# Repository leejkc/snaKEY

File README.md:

### todo list:

1. pcb borders
2. lcd/oled display
3. plate/case (3d print or order cnc)

### 50%, staggered, wired only

- **1** raspberry pi pico / pico2
- **47** diodes *(1N4148)*
- **47** switches
- **1** 2u plate mount stab (enter)
- **1** 6.25u plate mount stab
- keycaps

### LAYOUT:
[permalink to layout editor](https://www.keyboard-layout-editor.com/##@@=Esc&=Q&=W&=E&=R&=T&=Y&=U&=I&=O&=P&=%7B%0A%5B&=%7D%0A%5D&_x:0.25%3B&=Del%3B&@_w:1.25%3B&=Fn&=A&=S&=D&=F&=G&=H&=J&=K&=L&=%2F:%0A%2F%3B&=%22%0A'&_w:2%3B&=Enter%3B&@_w:1.75%3B&=Shift&=Z&=X&=C&=V&=B&=N&=M&=%3C%0A,&=%3E%0A.&=%3F%0A%2F%2F&=%E2%86%91&_w:1.5%3B&=%7C%0A%5C%3B&@_x:0.75&w:1.25%3B&=Ctrl&_w:1.25%3B&=Alt&_a:7&w:6.25%3B&=&_a:4&w:1.25%3B&=Super&=%E2%86%90&=%E2%86%93&=%E2%86%92)

note: **enter key has to be the 2u numberpad one**

### CAD DRAWINGS:

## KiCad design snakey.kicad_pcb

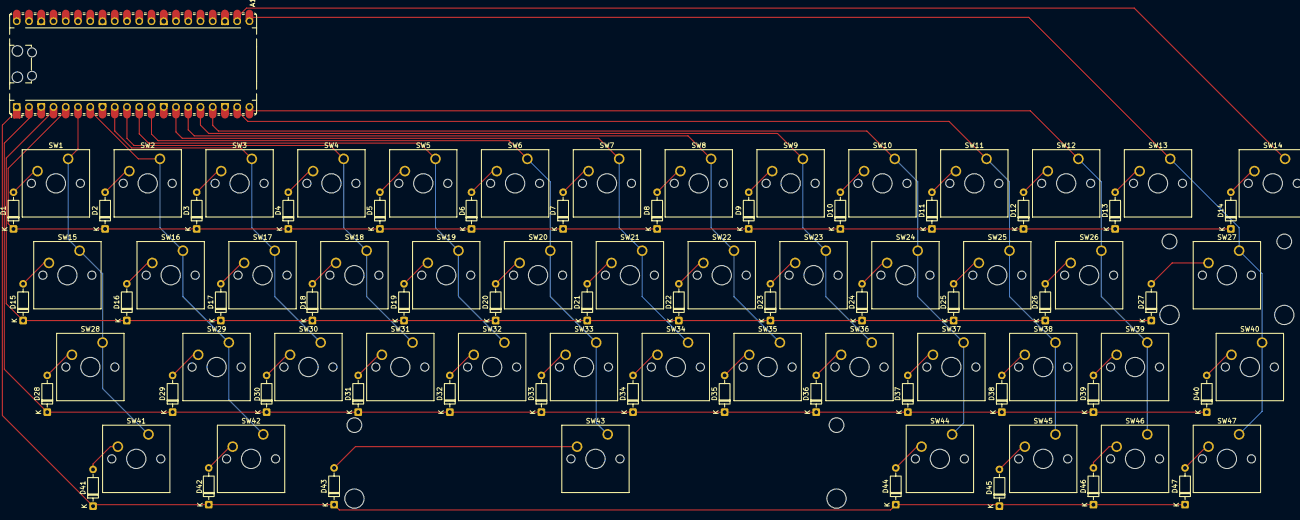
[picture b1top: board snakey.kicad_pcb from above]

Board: 2 copper layers, 95 parts (0 on the bottom side), 18 nets.

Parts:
A1: RaspberryPi_Pico; RaspberryPi_Pico_Common_Unspecified
D1, D2, D3, D4, D5, D6, D7, D8, D9, D10, D11, D12, D13, D14, D15, D16, D17, D18, D19, D20, D21, D22, D23, D24, D25, D26, D27, D28, D29, D30, D31, D32, D33, D34, D35, D36, D37, D38, D39, D40, D41, D42, D43, D44, D45, D46, D47: 1N4148; D_DO-35_SOD27_P7.62mm_Horizontal
SW1: ESC; SW_Cherry_MX_1.00u_PCB
SW2: q; SW_Cherry_MX_1.00u_PCB
SW3: w; SW_Cherry_MX_1.00u_PCB
SW4: e; SW_Cherry_MX_1.00u_PCB
SW5: r; SW_Cherry_MX_1.00u_PCB
SW6: t; SW_Cherry_MX_1.00u_PCB
SW7: y; SW_Cherry_MX_1.00u_PCB
SW8: u; SW_Cherry_MX_1.00u_PCB
SW9: i; SW_Cherry_MX_1.00u_PCB
SW10: o; SW_Cherry_MX_1.00u_PCB
SW11: p; SW_Cherry_MX_1.00u_PCB
SW12: [; SW_Cherry_MX_1.00u_PCB
SW13: ]; SW_Cherry_MX_1.00u_PCB
SW14: DEL; SW_Cherry_MX_1.00u_PCB
SW15: FN; SW_Cherry_MX_1.25u_PCB
SW16: a; SW_Cherry_MX_1.00u_PCB
SW17: s; SW_Cherry_MX_1.00u_PCB
SW18: d; SW_Cherry_MX_1.00u_PCB
SW19: f; SW_Cherry_MX_1.00u_PCB
SW20: g; SW_Cherry_MX_1.00u_PCB
SW21: h; SW_Cherry_MX_1.00u_PCB
SW22: j; SW_Cherry_MX_1.00u_PCB
SW23: k; SW_Cherry_MX_1.00u_PCB
SW24: l; SW_Cherry_MX_1.00u_PCB
SW25: ;; SW_Cherry_MX_1.00u_PCB
SW26: '; SW_Cherry_MX_1.00u_PCB
SW27: ENTER; SW_Cherry_MX_2.00u_PCB
SW28: SHIFT; SW_Cherry_MX_1.75u_PCB
SW29: z; SW_Cherry_MX_1.00u_PCB
SW30: x; SW_Cherry_MX_1.00u_PCB
SW31: c; SW_Cherry_MX_1.00u_PCB
SW32: v; SW_Cherry_MX_1.00u_PCB
SW33: b; SW_Cherry_MX_1.00u_PCB
SW34: n; SW_Cherry_MX_1.00u_PCB
SW35: m; SW_Cherry_MX_1.00u_PCB
SW36: ,; SW_Cherry_MX_1.00u_PCB
SW37: .; SW_Cherry_MX_1.00u_PCB
SW38: /; SW_Cherry_MX_1.00u_PCB
SW39: UP; SW_Cherry_MX_1.00u_PCB
SW40: \; SW_Cherry_MX_1.50u_PCB
SW41: CTRL; SW_Cherry_MX_1.25u_PCB
SW42: ALT; SW_Cherry_MX_1.25u_PCB
SW43: SPACE; SW_Cherry_MX_6.25u_PCB
SW44: SUPER; SW_Cherry_MX_1.25u_PCB
SW45: LEFT; SW_Cherry_MX_1.00u_PCB
SW46: DOWN; SW_Cherry_MX_1.00u_PCB
SW47: RIGHT; SW_Cherry_MX_1.00u_PCB

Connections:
Col1: A1.6 (GPIO4), D1.2 (A), D15.2 (A), D28.2 (A), D41.2 (A), SW1.1 (A), SW1.2 (A), SW15.1 (A), SW15.2 (A), SW28.1 (A), SW28.2 (A), SW41.1 (A), SW41.2 (A)
Col2: A1.7 (GPIO5), D2.2 (A), D16.2 (A), D29.2 (A), D42.2 (A), SW2.1 (A), SW2.2 (A), SW16.1 (A), SW16.2 (A), SW29.1 (A), SW29.2 (A), SW42.1 (A), SW42.2 (A)
Col3: A1.9 (GPIO6), D3.2 (A), D17.2 (A), D30.2 (A), SW3.1 (A), SW3.2 (A), SW17.1 (A), SW17.2 (A), SW30.1 (A), SW30.2 (A)
Col4: A1.10 (GPIO7), D4.2 (A), D18.2 (A), D31.2 (A), SW4.1 (A), SW4.2 (A), SW18.1 (A), SW18.2 (A), SW31.1 (A), SW31.2 (A)
Col5: A1.11 (GPIO8), D5.2 (A), D19.2 (A), D32.2 (A), SW5.1 (A), SW5.2 (A), SW19.1 (A), SW19.2 (A), SW32.1 (A), SW32.2 (A)
Col6: A1.12 (GPIO9), D6.2 (A), D20.2 (A), D33.2 (A), D43.2 (A), SW6.1 (A), SW6.2 (A), SW20.1 (A), SW20.2 (A), SW33.1 (A), SW33.2 (A), SW43.1 (A), SW43.2 (A)
Col7: A1.14 (GPIO10), D7.2 (A), D21.2 (A), D34.2 (A), SW7.1 (A), SW7.2 (A), SW21.1 (A), SW21.2 (A), SW34.1 (A), SW34.2 (A)
Col8: A1.15 (GPIO11), D8.2 (A), D22.2 (A), D35.2 (A), SW8.1 (A), SW8.2 (A), SW22.1 (A), SW22.2 (A), SW35.1 (A), SW35.2 (A)
Col9: A1.16 (GPIO12), D9.2 (A), D23.2 (A), D36.2 (A), SW9.1 (A), SW9.2 (A), SW23.1 (A), SW23.2 (A), SW36.1 (A), SW36.2 (A)
Col10: A1.17 (GPIO13), D10.2 (A), D24.2 (A), D37.2 (A), D44.2 (A), SW10.1 (A), SW10.2 (A), SW24.1 (A), SW24.2 (A), SW37.1 (A), SW37.2 (A), SW44.1 (A), SW44.2 (A)
Col11: A1.19 (GPIO14), D11.2 (A), D25.2 (A), D38.2 (A), D45.2 (A), SW11.1 (A), SW11.2 (A), SW25.1 (A), SW25.2 (A), SW38.1 (A), SW38.2 (A), SW45.1 (A), SW45.2 (A)
Col12: A1.20 (GPIO15), D12.2 (A), D26.2 (A), D39.2 (A), D46.2 (A), SW12.1 (A), SW12.2 (A), SW26.1 (A), SW26.2 (A), SW39.1 (A), SW39.2 (A), SW46.1 (A), SW46.2 (A)
Col13: A1.21 (GPIO16), D13.2 (A), D27.2 (A), D40.2 (A), D47.2 (A), SW13.1 (A), SW13.2 (A), SW27.1 (A), SW27.2 (A), SW40.1 (A), SW40.2 (A), SW47.1 (A), SW47.2 (A)
Col14: A1.22 (GPIO17), D14.2 (A), SW14.1 (A), SW14.2 (A)
Row1: A1.5 (GPIO3), D1.1 (K), D2.1 (K), D3.1 (K), D4.1 (K), D5.1 (K), D6.1 (K), D7.1 (K), D8.1 (K), D9.1 (K), D10.1 (K), D11.1 (K), D12.1 (K), D13.1 (K), D14.1 (K)
Row2: A1.4 (GPIO2), D15.1 (K), D16.1 (K), D17.1 (K), D18.1 (K), D19.1 (K), D20.1 (K), D21.1 (K), D22.1 (K), D23.1 (K), D24.1 (K), D25.1 (K), D26.1 (K), D27.1 (K)
Row3: A1.2 (GPIO1), D28.1 (K), D29.1 (K), D30.1 (K), D31.1 (K), D32.1 (K), D33.1 (K), D34.1 (K), D35.1 (K), D36.1 (K), D37.1 (K), D38.1 (K), D39.1 (K), D40.1 (K)
Row4: A1.1 (GPIO0), D41.1 (K), D42.1 (K), D43.1 (K), D44.1 (K), D45.1 (K), D46.1 (K), D47.1 (K)

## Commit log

2026-01-12 initial idea
2026-01-12 add link from editor & fix embed path
2026-01-12 add toggle swithc
2026-01-12 Remove short toggle switch
2026-01-12 kicad proj
2026-01-12 add kiswitch module
2026-01-12 stab count correction
2026-01-12 add pico template
2026-01-12 layout instructions
    Added note about using tab as enter and enter as layer ctrl.
2026-01-12 whitespace
2026-01-12 whitespace
    Added note about using tab as enter and enter as layer ctrl.
2026-01-12 update README.md
    Updated the permalink to the layout editor and clarified the enter key requirement.
2026-01-12 updated layout
2026-01-12 Update .gitignore to exclude auto-saved files
2026-01-12 Remove kiswitch submodule from .gitmodules
2026-01-12 keyboard schematic update
2026-01-12 mostly done schematic
2026-01-12 images for readme
2026-01-12 kicad images
2026-01-12 Change todo list to numbered format
    Updated todo list formatting to numbered items.
2026-01-15 remove title
